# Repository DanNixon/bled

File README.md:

<h1 align="center">BLED</h1>

<p align="center">
  Versatile control board for WS2812 compatible LED fixtures.
  Using WebAssembly for effects and Bluetooth Low Energy for control.
</p>

---

**BLED is a work in progress.** Although mostly feature complete, specifics of the effect API are subject to change.
The web UI is likely to undergo significant changes, the current version is a mostly vibe coded prototype.

Documentation can be found in [`docs/README.md`](docs/README.md).

## Downloads

Pre-built artifacts from the latest [`main` CI build](https://github.com/dannixon/bled/actions/workflows/ci.yml?query=branch%3Amain+event%3Apush):

- [Firmware (`.uf2` images)](https://nightly.link/dannixon/bled/workflows/ci/main/firmware.zip)
- [Effects (WebAssembly modules and presets)](https://nightly.link/dannixon/bled/workflows/ci/main/effects.zip)

## Building effects

[`bled-effect`](lib/effect/README.md) is a helper library for building BLED effects in Rust and compiling them to WebAssembly. The [`effects`](effects) directory contains example effect crates.

## License

The project is licensed under the MIT License, see [`LICENSE.txt`](LICENSE.txt).

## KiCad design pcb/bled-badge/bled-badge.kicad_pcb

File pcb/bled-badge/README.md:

# Badge LED panel

A badge sized LED panel that takes a [BLED Stamp](../bled-stamp).

## Configuration

Load this `fixtures.json` onto the SD card to configure a BLED Stamp for the Badge PCB.

Adjust the `limit` mode as required.
Don't increase the intensity much above the default values: they quickly become blinding when viewed as a badge, generate a lot of heat and will deplete the battery very rapidly (but it would make a very good emergency torch if required).

```json
[
  {
    "name": "onboard",
    "layout": {
      "linear_array": {}
    },
    "spans": [
      {"name": "led", "channel": 0, "start": 0, "length": 1, "limit": {"mode": "clamp", "limit": {"r": 31, "g": 31, "b": 31}}},
      {"name": "led", "channel": 1, "start": 0, "length": 1, "limit": {"mode": "clamp", "limit": {"r": 31, "g": 31, "b": 31}}},
      {"name": "led", "channel": 2, "start": 0, "length": 1, "limit": {"mode": "clamp", "limit": {"r": 31, "g": 31, "b": 31}}},
      {"name": "led", "channel": 3, "start": 0, "length": 1, "limit": {"mode": "clamp", "limit": {"r": 31, "g": 31, "b": 31}}}
    ]
  },
  {
    "name": "badge",
    "layout": {
      "matrix2d": {
        "width": 50,
        "height": 12,
        "origin": "TopLeft",
        "layout": "RowMajor",
        "wiring_order": "Serpentine"
      }
    },
    "spans": [
      {"name": "top",     "channel": 3, "start": 1, "length": 150, "limit": {"mode": "clamp", "limit": {"r": 7, "g": 7, "b": 7}}},
      {"name": "up-mid",  "channel": 1, "start": 1, "length": 150, "limit": {"mode": "clamp", "limit": {"r": 7, "g": 7, "b": 7}}},
      {"name": "low-mid", "channel": 2, "start": 1, "length": 150, "limit": {"mode": "clamp", "limit": {"r": 7, "g": 7, "b": 7}}},
      {"name": "bottom",  "channel": 0, "start": 1, "length": 150, "limit": {"mode": "clamp", "limit": {"r": 7, "g": 7, "b": 7}}}
    ]
  }
]
```

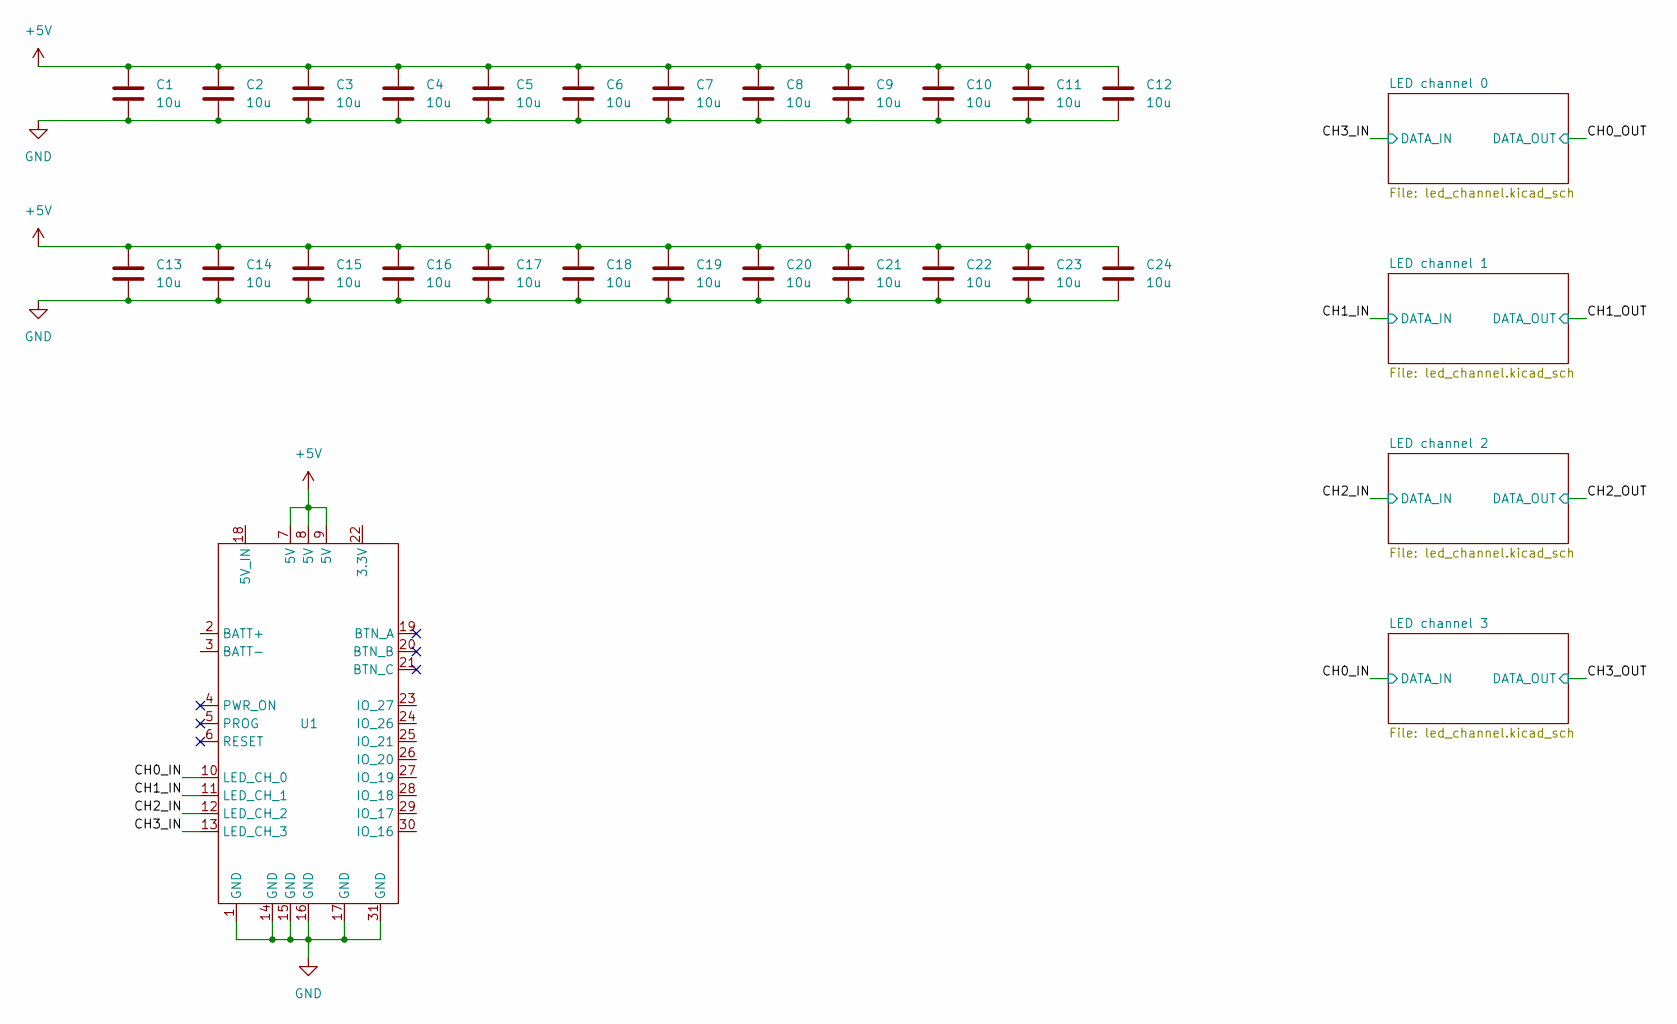
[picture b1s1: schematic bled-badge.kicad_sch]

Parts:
C1, C2, C3, C4, C5, C6, C7, C8, C9, C10, C11, C12, C13, C14, C15, C16, C17, C18, C19, C20, C21, C22, C23, C24: 10u; C_0402_1005Metric; LCSC C15525
U1: BLED_Stamp

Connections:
+5V: C1.1, C2.1, C3.1, C4.1, C5.1, C6.1, C7.1, C8.1, C9.1, C10.1, C11.1, C12.1, C13.1, C14.1, C15.1, C16.1, C17.1, C18.1, C19.1, C20.1, C21.1, C22.1, C23.1, C24.1, U1.7 (5V), U1.8 (5V), U1.9 (5V); also elsewhere on the board
/CH0_IN: U1.10 (LED_CH_0); also elsewhere on the board
/CH1_IN: U1.11 (LED_CH_1); also elsewhere on the board
/CH2_IN: U1.12 (LED_CH_2); also elsewhere on the board
/CH3_IN: U1.13 (LED_CH_3); also elsewhere on the board
GND: C1.2, C2.2, C3.2, C4.2, C5.2, C6.2, C7.2, C8.2, C9.2, C10.2, C11.2, C12.2, C13.2, C14.2, C15.2, C16.2, C17.2, C18.2, C19.2, C20.2, C21.2, C22.2, C23.2, C24.2, U1.1 (GND), U1.14 (GND), U1.15 (GND), U1.16 (GND), U1.17 (GND), U1.31 (GND); also elsewhere on the board
